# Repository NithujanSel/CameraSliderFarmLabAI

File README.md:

# Camera slider IoT Project

### Student 1: Nithujan Selvaratnam

### Student 2: Jesse Denaux

### Student 3: Tarun Singh

<a href="https://nithujansel.github.io/CameraSliderFarmLabAI/#/">Docsify Page</a><br>

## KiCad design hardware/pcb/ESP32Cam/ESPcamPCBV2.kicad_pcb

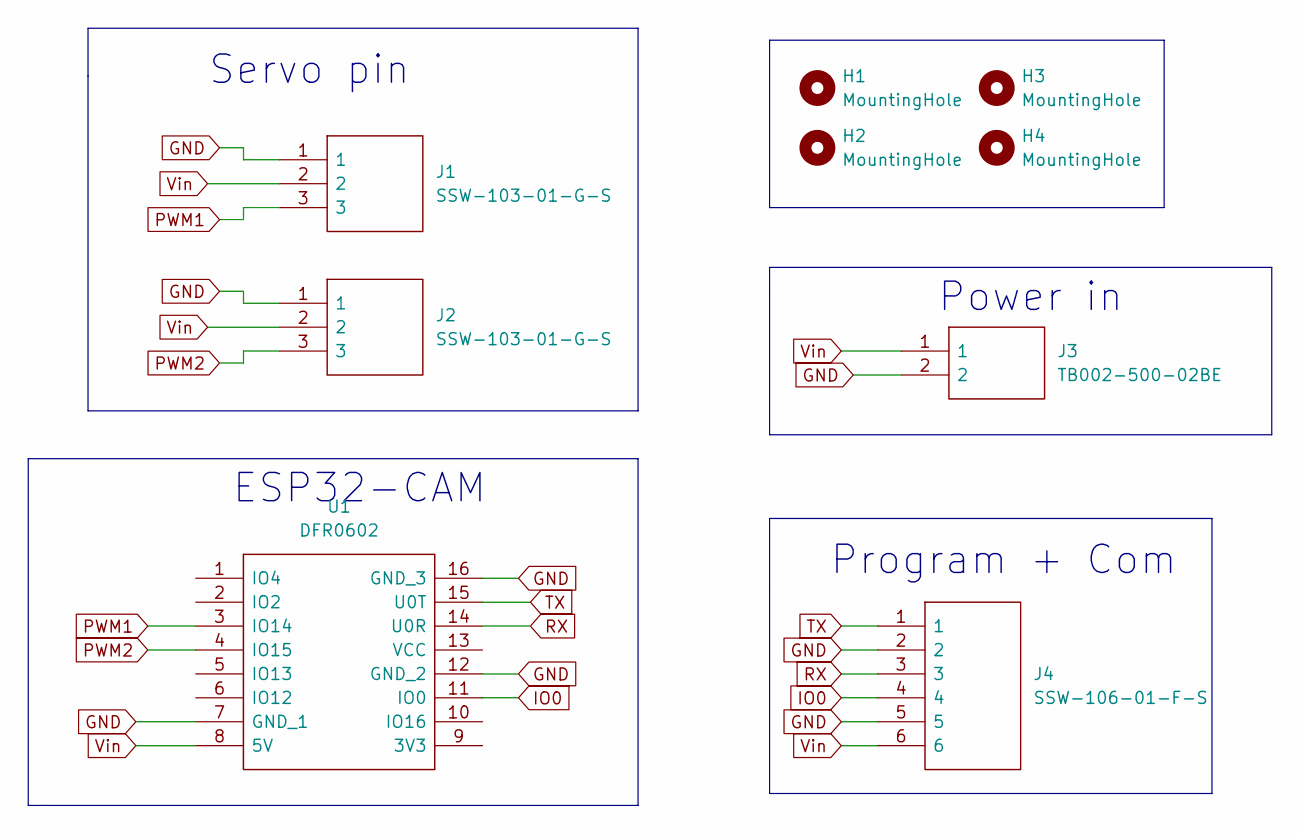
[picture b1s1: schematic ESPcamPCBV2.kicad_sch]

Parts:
H1, H2, H3, H4: MountingHole; MountingHole_3.2mm_M3
J1, J2: SSW-103-01-G-S; RHDR3W64P0X254_1X3_813X241X851P; Manufacturer_Part_Number SSW-103-01-G-S; Mouser Part Number 200-SSW10301GS
J3: TB002-500-02BE; TB00250002BE; Manufacturer_Part_Number TB002-500-02BE; Mouser Part Number 490-TB002-500-02BE
J4: SSW-106-01-F-S; RHDR6W79P0X254_1X6_1575X241X851P; Manufacturer_Part_Number SSW-106-01-F-S; Mouser Part Number 200-SSW10601FS
U1: DFR0602; Manufacturer_Part_Number DFR0602; Mouser Part Number 426-DFR0602

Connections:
GND: J1.1, J2.1, J3.2, J4.2, J4.5, U1.7 (GND_1), U1.12 (GND_2), U1.16 (GND_3)
IO0: J4.4, U1.11 (IO0)
PWM1: J1.3, U1.3 (IO14)
PWM2: J2.3, U1.4 (IO15)
RX: J4.3, U1.14 (U0R)
TX: J4.1, U1.15 (U0T)
Vin: J1.2, J2.2, J3.1, J4.6, U1.8 (5V)

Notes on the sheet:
Servo pin
ESP32-CAM
Power in
Program + Com

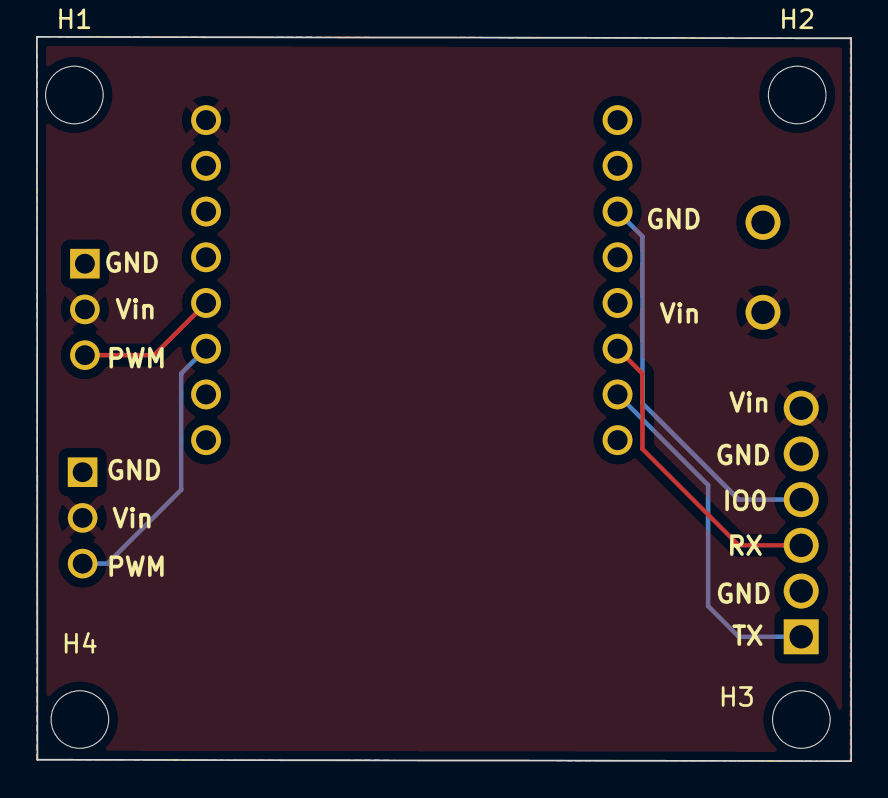
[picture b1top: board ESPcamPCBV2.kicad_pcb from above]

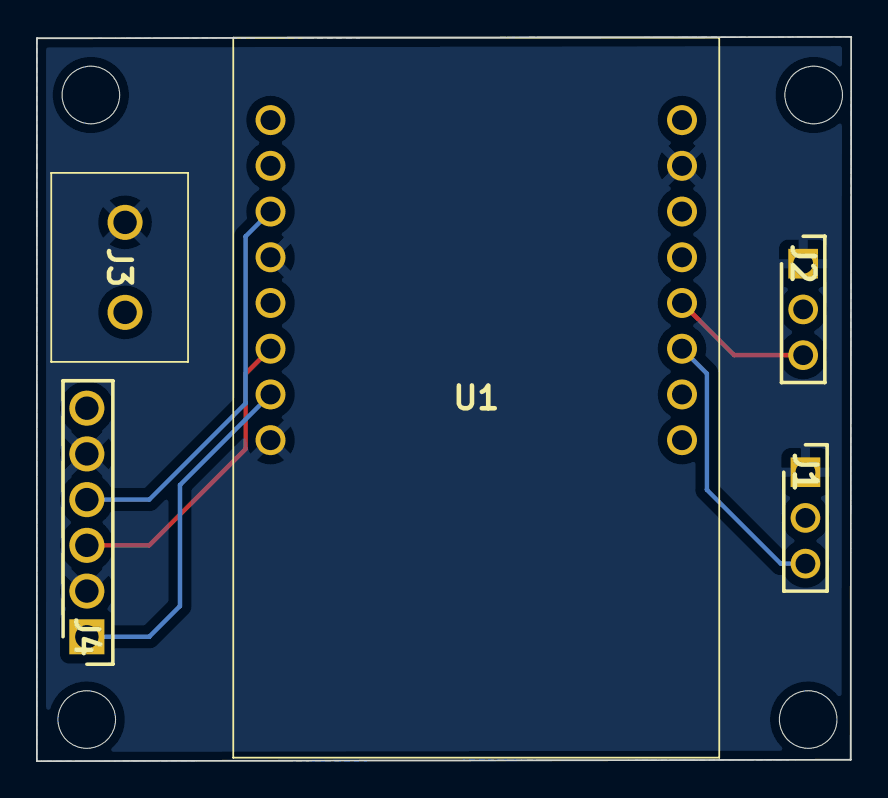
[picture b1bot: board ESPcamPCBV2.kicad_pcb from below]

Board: 2 copper layers, 45.2 x 40.2 mm, 9 parts (5 on the bottom side), 7 nets.

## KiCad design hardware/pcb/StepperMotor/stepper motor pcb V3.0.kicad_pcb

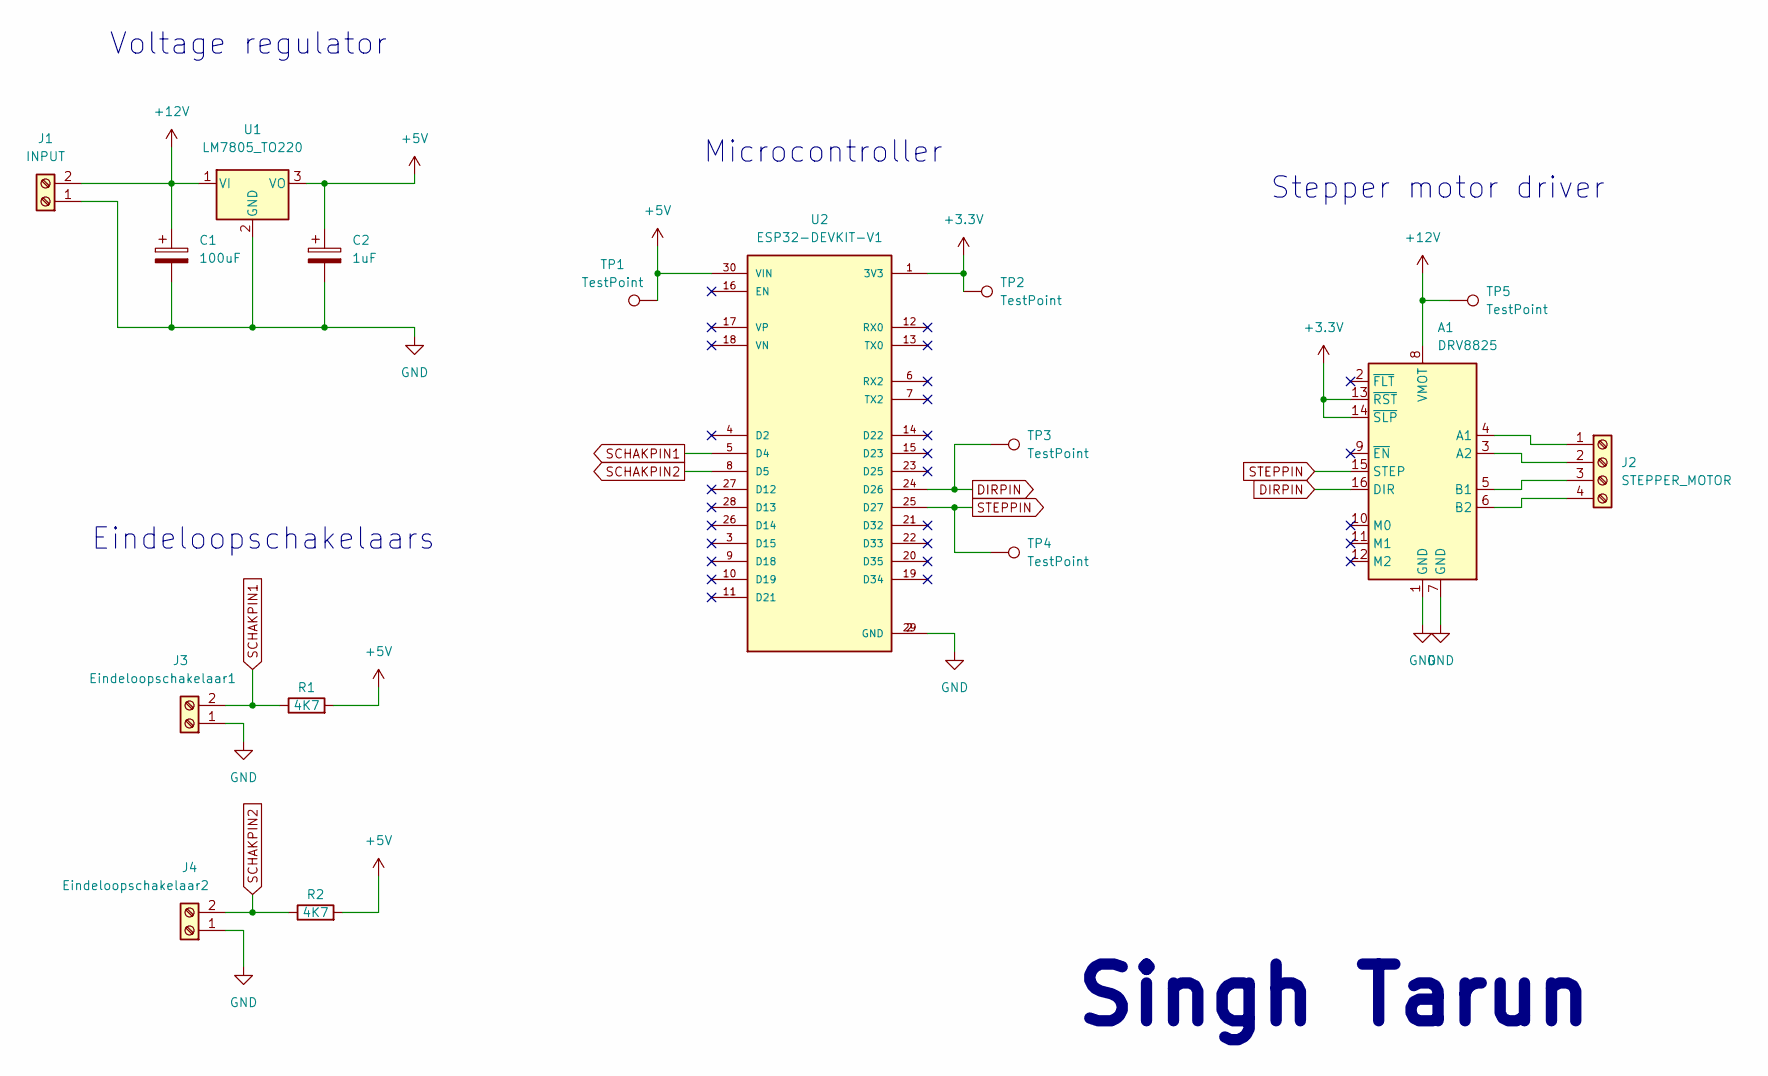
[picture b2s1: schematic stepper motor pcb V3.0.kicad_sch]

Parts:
A1: DRV8825; Pololu_Breakout-16_15.2x20.3mm
C1: 100uF; CP_Radial_D10.0mm_P3.80mm
C2: 1uF; CP_Radial_D10.0mm_P3.80mm
J1: INPUT; TerminalBlock_bornier-2_P5.08mm
J2: STEPPER_MOTOR; TerminalBlock_bornier-4_P5.08mm
J3: Eindeloopschakelaar1; PinHeader_1x02_P2.54mm_Vertical
J4: Eindeloopschakelaar2; PinHeader_1x02_P2.54mm_Vertical
R1, R2: 4K7; R_Axial_DIN0309_L9.0mm_D3.2mm_P15.24mm_Horizontal
TP1, TP2, TP3, TP4, TP5: TestPoint; TestPoint_Pad_D2.0mm
U1: LM7805_TO220; TO-220-3_Vertical
U2: ESP32-DEVKIT-V1; ESP32_DEVKIT_V1; PARTREV N/A

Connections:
+3.3V: A1.13 (~RST), A1.14 (~SLP), TP2.1, U2.1 (3V3)
+5V: C2.1, R1.2, R2.2, TP1.1, U1.3 (VO), U2.30 (VIN)
+12V: A1.8 (VMOT), C1.1, J1.2, TP5.1, U1.1 (VI)
DIRPIN: A1.16 (DIR), TP3.1, U2.24 (D26)
GND: A1.1 (GND), A1.7 (GND), C1.2, C2.2, J1.1, J3.1, J4.1, U1.2 (GND), U2.2 (GND), U2.29 (GND)
unnamed: A1.4 (A1), J2.1
unnamed: A1.3 (A2), J2.2
unnamed: A1.5 (B1), J2.3
unnamed: A1.6 (B2), J2.4
SCHAKPIN1: J3.2, R1.1, U2.5 (D4)
SCHAKPIN2: J4.2, R2.1, U2.8 (D5)
STEPPIN: A1.15 (STEP), TP4.1, U2.25 (D27)

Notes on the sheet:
Microcontroller
Stepper motor driver
Voltage regulator
Eindeloopschakelaars
Singh Tarun

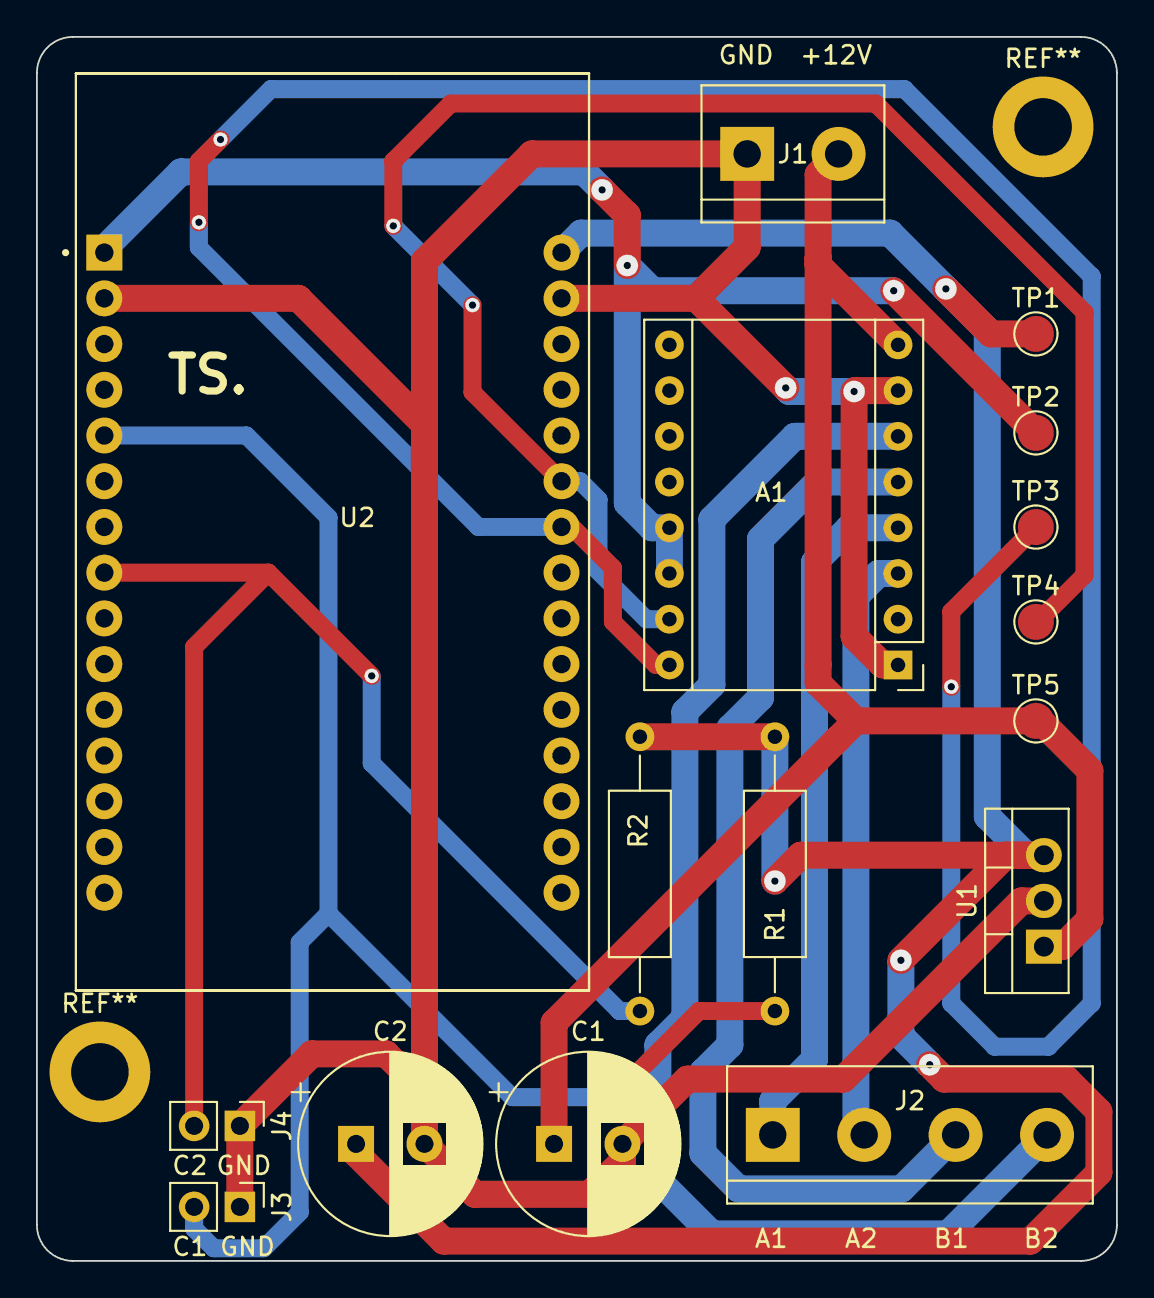
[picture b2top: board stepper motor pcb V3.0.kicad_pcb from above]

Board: 2 copper layers, 60.0 x 68.0 mm, 16 parts (0 on the bottom side), 12 nets.

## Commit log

2023-01-19 Versie 1
2023-01-19 Laaster Versie v2
